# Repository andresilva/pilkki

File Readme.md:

# Pilkki
SWD flashing tool for EFM32 microcontrollers.

## Project structure

Utility to interact with flasher could be found in [software](software) folder.

Schematics and PCB (KiCAD) are in [electronics](electronics) folder.

Firmware sources are [here](firmware)

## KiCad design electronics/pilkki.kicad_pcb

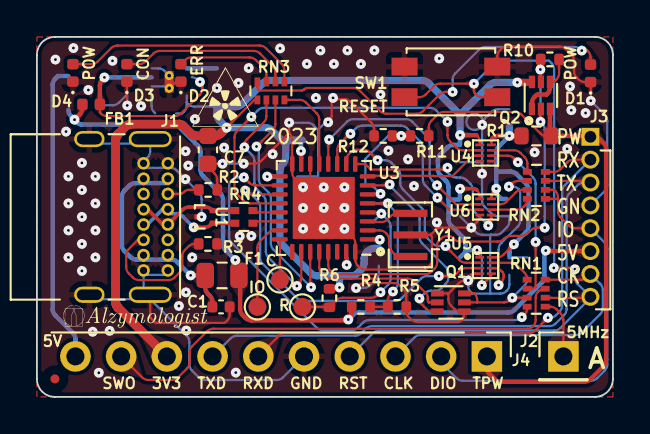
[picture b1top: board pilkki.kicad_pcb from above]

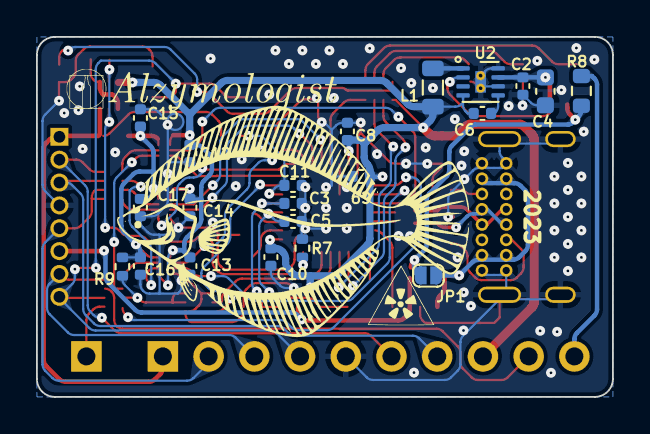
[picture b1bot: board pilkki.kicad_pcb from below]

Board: 2 copper layers, 32.0 x 20.0 mm, 58 parts (21 on the bottom side), 57 nets.

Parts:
C1, C2, C3, C5, C8, C9, C10, C11, C12, C13, C14, C15, C16, C17: 0.1u; C_0402_1005Metric
C4, C7: 4.7uFx6.3; C_0603_1608Metric
C6: 560pF; C_0402_1005Metric
D1: GREEN; LED_0402_1005Metric
D2: RED; LED_0402_1005Metric
D3: ORANGE; LED_0402_1005Metric
D4: YELLOW; LED_0402_1005Metric
F1: 0ZCK0100FF2E; Fuse_0805_2012Metric
FB1: BLM15AG102SZ1D; L_0402_1005Metric
FID1: Fiducial; Fiducial_0.5mm_Mask1.5mm
J1: USB_C_Receptacle; USB_C_Receptacle_GCT_USB4085
J2: Conn_01x01_Pin; PinHeader_1x01_P2.54mm_Vertical
J3: Conn_01x08; PinHeader_1x08_P1.27mm_Vertical
J4: Conn_01x10; PinHeader_1x10_P2.54mm_Vertical
JP1: SolderJumper_2_Open; SolderJumper_0.8.x1mm
L1: LQM21PN1R0MC0D; L_0805_2012Metric
Q1: SSM6N35AFE; SOT-563
Q2: DMG1023UV; SOT-563
R1: 10R; R_0603_1608Metric
R2, R3: 5.1K; R_0402_1005Metric
R4, R11: 4.7K; R_0402_1005Metric
R5, R6, R7, R9, R10, R12: 10K; R_0402_1005Metric
R8: 4.7R; R_0603_1608Metric
RN1, RN2: 100; R_Array_Concave_4x0402
RN3: 330; R_Array_Concave_4x0402
RN4: 33; R_Array_Convex_2x0402
SW1: EVQ-P2202M
SWDCK1: TestPoint; TestPoint_Pad_D1.0mm
SWDIO1: TestPoint; TestPoint_Pad_D1.0mm
U1: TPD2EUSB30A; Texas_DRT-3
U2: MIC23050-SYML; Micrel_MLF-8-1EP_2x2mm_P0.5mm_EP0.6x1.2mm_ThermalVias
U3: STM32G431KBUx; QFN-32-1EP_5x5mm_P0.5mm_EP3.45x3.45mm
U4, U5, U6: 74LVC2T45RA3; DFN1210-8
Y1: ECS-CTP-8.00-30; Resonator_SMD_Murata_CSTxExxV-3Pin_3.0x1.1mm

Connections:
3V3: C6.1, C7.2, C8.1, C9.1, C10.1, C12.1, C13.1, C14.1, J4.8, L1.2, Q2.6 (D), R6.2, RN3.5 (R4.2), U2.4 (SNS), U3.1 (VDD), U3.15 (VDDA), U3.17 (VDD), U4.1 (VCCA), U5.1 (VCCA), U5.5 (DIR), U6.1 (VCCA)
/CC1: J1.A5 (CC1), R2.2
/CC2: J1.B5 (CC2), R3.2
/D_N: J1.A7 (D-), J1.B7 (D-), RN4.1 (R1.1), U1.2 (D-)
/D_P: J1.A6 (D+), J1.B6 (D+), RN4.2 (R2.1), U1.1 (D+)
/LED0: RN3.8 (R1.2), U3.13 (PB0)
/LED1: RN3.6 (R3.2), U3.26 (PB3)
/LED2: RN3.7 (R2.2), U3.27 (PB4)
/PWRBR: Q2.2 (G), Q2.5 (G), R10.1, U3.29 (PB6)
/RST: J3.8, J4.4, RN1.2 (R2.1), SW1.2
/RXD: J3.2, J4.6, RN2.4 (R4.1)
/SWCLK: J3.7, J4.3, RN1.4 (R4.1)
/SWDIO: J3.5, J4.2, RN2.1 (R1.1), RN2.2 (R2.1)
/SWDIR: U3.9 (PA4), U6.5 (DIR)
/SWO: J4.9, RN1.3 (R3.1)
/TPWR_C: C11.1, R11.2, R12.1, U3.6 (PA1)
/TXD: J3.3, J4.7, RN2.3 (R3.1)
/V_BUS: C3.1, R4.2, R5.1, U3.5 (PA0)
/iMCO: RN1.8 (R1.2), U3.18 (PA8)
/iRST: Q1.2 (G), U3.28 (PB5)
/iRST_S: Q1.3 (D), U3.7 (PA2)
/iRXD: U3.20 (PA10), U4.2 (1A)
/iSWCLK: U3.10 (PA5), U5.2 (1A)
/iSWDIN: U3.11 (PA6), U6.3 (2A)
/iSWDO: U3.12 (PA7), U6.2 (1A)
/iSWO: U3.8 (PA3), U4.3 (2A)
/iTXD: U3.19 (PA9), U5.3 (2A)
/xRST: Q1.5 (G), Q1.6 (D), R9.1, RN1.7 (R2.2)
/xRXD: RN2.5 (R4.2), U4.7 (1B)
/xSWCLK: RN1.5 (R4.2), U5.7 (1B)
/xSWDIN: RN2.8 (R1.2), U6.6 (2B)
/xSWDO: RN2.7 (R2.2), U6.7 (1B)
/xSWO: RN1.6 (R3.2), U4.6 (2B)
/xTXD: RN2.6 (R3.2), U5.6 (2B)
GND: C1.2, C2.2, C3.2, C4.1, C5.2, C7.1, C8.2, C9.2, C10.2, C11.2, C12.2, C13.2, C14.2, C15.2, C16.2, C17.2, D1.1 (K), D2.1 (K), D3.1 (K), D4.1 (K), J1.A1 (GND), J1.A12 (GND), J1.B1 (GND), J1.B12 (GND), J1.S1 (SHIELD), J3.4, J4.5, Q1.1 (S), Q1.4 (S), R2.1, R3.1, R5.2, R7.1, R12.2, SW1.1, U1.3 (GND), U2.6 (AGND), U2.8 (PGND), U2.9 (EP_GND), U3.14 (VSSA), U3.16 (VSS), U3.32 (VSS), U3.33 (VSS), U4.4 (GND), U4.5 (DIR), U5.4 (GND), U6.4 (GND), Y1.2
unnamed: D1.2 (A), RN3.4 (R4.1)
unnamed: D2.2 (A), RN3.3 (R3.1)
unnamed: D3.2 (A), RN3.2 (R2.1)
unnamed: D4.2 (A), RN3.1 (R1.1)
unnamed: J2.1, RN1.1 (R1.1)
unnamed: J4.10, R8.1
unnamed: C1.1, F1.1, J1.A4 (VBUS), J1.A9 (VBUS), J1.B4 (VBUS), J1.B9 (VBUS), JP1.2 (B)
unnamed: Q2.1 (S), Q2.4 (S), R10.2
unnamed: RN4.4 (R1.2), U3.21 (PA11)
unnamed: RN4.3 (R2.2), U3.22 (PA12)
unnamed: C6.2, U2.5 (CFF)
unnamed: C2.1, C4.2, FB1.2, U2.2 (EN), U2.7 (VIN)
unnamed: L1.1, U2.1 (SW)
unnamed: SWDIO1.1, U3.23 (PA13)
unnamed: SWDCK1.1, U3.24 (PA14)
unnamed: R7.2, U3.31 (PB8)
unnamed: U3.2 (PF0), Y1.1
unnamed: U3.3 (PF1), Y1.3
unnamed: C5.1, R6.1, U3.4 (PG10)
TPWR: J3.1, J4.1, Q2.3 (D), R1.1, R11.1
USB_P: F1.2, FB1.1, J3.6, JP1.1 (A), R4.1, R8.2
xTPWR: C15.1, C16.1, C17.1, R1.2, R9.2, U4.8 (VCCB), U5.8 (VCCB), U6.8 (VCCB)

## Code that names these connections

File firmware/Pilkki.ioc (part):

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Mcu.Name=STM32G431K(6-8-B)Ux
Mcu.Package=UFQFPN32
Mcu.UserName=STM32G431KBUx
PA0.Mode=IN1-Single-Ended
PA0.Signal=ADC1_IN1
PA1.Mode=IN2-Single-Ended
PA1.Signal=ADC1_IN2
PA10.Mode=Asynchronous
PA10.Signal=USART1_RX
PA11.Mode=Device
PA11.Signal=USB_DM
PA12.Mode=Device
PA12.Signal=USB_DP
PA13.Mode=Serial_Wire
PA13.Signal=SYS_JTMS-SWDIO
PA14.Mode=Serial_Wire
PA14.Signal=SYS_JTCK-SWCLK
PA2.Mode=Asynchronous
PA2.Signal=USART2_TX
PA3.Mode=Asynchronous
PA3.Signal=USART2_RX
PA4.GPIOParameters=GPIO_Speed,PinState,GPIO_PuPd,GPIO_Label,GPIO_ModeDefaultOutputPP
PA4.GPIO_Label=SWDIR
PA4.GPIO_ModeDefaultOutputPP=GPIO_MODE_OUTPUT_PP
PA4.GPIO_PuPd=GPIO_NOPULL
PA4.GPIO_Speed=GPIO_SPEED_FREQ_VERY_HIGH
PA4.PinState=GPIO_PIN_RESET
PA4.Signal=GPIO_Output
PA5.GPIOParameters=GPIO_Speed
PA5.GPIO_Speed=GPIO_SPEED_FREQ_VERY_HIGH
PA5.Mode=Full_Duplex_Master
PA5.Signal=SPI1_SCK
PA6.GPIOParameters=GPIO_Speed,GPIO_PuPd
PA6.GPIO_PuPd=GPIO_PULLUP
PA6.GPIO_Speed=GPIO_SPEED_FREQ_VERY_HIGH
PA6.Mode=Full_Duplex_Master
PA6.Signal=SPI1_MISO
PA7.GPIOParameters=GPIO_Speed
PA7.GPIO_Speed=GPIO_SPEED_FREQ_VERY_HIGH
PA7.Mode=Full_Duplex_Master
PA7.Signal=SPI1_MOSI
PA8.Mode=Clock-out
PA8.Signal=RCC_MCO
PA9.Mode=Asynchronous
PA9.Signal=USART1_TX
PB0.GPIOParameters=GPIO_Label
PB0.GPIO_Label=LED0
PB0.Signal=GPIO_Output
PB3.GPIOParameters=GPIO_Label
PB3.GPIO_Label=LED1
PB3.Signal=GPIO_Output
PB4.GPIOParameters=GPIO_Label
PB4.GPIO_Label=LED2
PB4.Signal=GPIO_Output
PB5.GPIOParameters=GPIO_Label
PB5.GPIO_Label=iRST
PB5.Signal=GPIO_Output
PB6.GPIOParameters=PinState,GPIO_Label
PB6.GPIO_Label=PWR_BRR
PB6.PinState=GPIO_PIN_SET
PB6.Signal=GPIO_Output
PF0-OSC_IN.Mode=HSE-External-Oscillator
PF0-OSC_IN.Signal=RCC_OSC_IN
PF1-OSC_OUT.Mode=HSE-External-Oscillator
PF1-OSC_OUT.Signal=RCC_OSC_OUT
RCC.HSE_VALUE=20000000
RCC.SYSCLKFreq_VALUE=170000000
RCC.SYSCLKSource=RCC_SYSCLKSOURCE_PLLCLK
board=custom

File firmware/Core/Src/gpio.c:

/* USER CODE BEGIN Header */
/**
  ******************************************************************************
  * @file    gpio.c
  * @brief   This file provides code for the configuration
  *          of all used GPIO pins.
  ******************************************************************************
  * @attention
  *
  * Copyright (c) 2023 STMicroelectronics.
  * All rights reserved.
  *
  * This software is licensed under terms that can be found in the LICENSE file
  * in the root directory of this software component.
  * If no LICENSE file comes with this software, it is provided AS-IS.
  *
  ******************************************************************************
  */
/* USER CODE END Header */

/* Includes ------------------------------------------------------------------*/
#include "gpio.h"

/* USER CODE BEGIN 0 */

/* USER CODE END 0 */

/*----------------------------------------------------------------------------*/
/* Configure GPIO                                                             */
/*----------------------------------------------------------------------------*/
/* USER CODE BEGIN 1 */

/* USER CODE END 1 */

/** Configure pins as
        * Analog
        * Input
        * Output
        * EVENT_OUT
        * EXTI
        * Free pins are configured automatically as Analog (this feature is enabled through
        * the Code Generation settings)
     PA8   ------> RCC_MCO
*/
void MX_GPIO_Init(void)
{

  GPIO_InitTypeDef GPIO_InitStruct = {0};

  /* GPIO Ports Clock Enable */
  __HAL_RCC_GPIOF_CLK_ENABLE();
  __HAL_RCC_GPIOG_CLK_ENABLE();
  __HAL_RCC_GPIOA_CLK_ENABLE();
  __HAL_RCC_GPIOB_CLK_ENABLE();

  /*Configure GPIO pin Output Level */
  HAL_GPIO_WritePin(SWDIR_GPIO_Port, SWDIR_Pin, GPIO_PIN_RESET);

  /*Configure GPIO pin Output Level */
  HAL_GPIO_WritePin(GPIOB, LED0_Pin|LED1_Pin|LED2_Pin|iRST_Pin, GPIO_PIN_RESET);

  /*Configure GPIO pin Output Level */
  HAL_GPIO_WritePin(PWR_BRR_GPIO_Port, PWR_BRR_Pin, GPIO_PIN_SET);

  /*Configure GPIO pin : PG10 */
  GPIO_InitStruct.Pin = GPIO_PIN_10;
  GPIO_InitStruct.Mode = GPIO_MODE_ANALOG;
  GPIO_InitStruct.Pull = GPIO_NOPULL;
  HAL_GPIO_Init(GPIOG, &GPIO_InitStruct);

  /*Configure GPIO pin : PtPin */
  GPIO_InitStruct.Pin = SWDIR_Pin;
  GPIO_InitStruct.Mode = GPIO_MODE_OUTPUT_PP;
  GPIO_InitStruct.Pull = GPIO_NOPULL;
  GPIO_InitStruct.Speed = GPIO_SPEED_FREQ_VERY_HIGH;
  HAL_GPIO_Init(SWDIR_GPIO_Port, &GPIO_InitStruct);

  /*Configure GPIO pins : PBPin PBPin PBPin PBPin
                           PBPin */
  GPIO_InitStruct.Pin = LED0_Pin|LED1_Pin|LED2_Pin|iRST_Pin
                          |PWR_BRR_Pin;
  GPIO_InitStruct.Mode = GPIO_MODE_OUTPUT_PP;
  GPIO_InitStruct.Pull = GPIO_NOPULL;
  GPIO_InitStruct.Speed = GPIO_SPEED_FREQ_LOW;
  HAL_GPIO_Init(GPIOB, &GPIO_InitStruct);

  /*Configure GPIO pin : PA8 */
  GPIO_InitStruct.Pin = GPIO_PIN_8;
  GPIO_InitStruct.Mode = GPIO_MODE_AF_PP;
  GPIO_InitStruct.Pull = GPIO_NOPULL;
  GPIO_InitStruct.Speed = GPIO_SPEED_FREQ_LOW;
  GPIO_InitStruct.Alternate = GPIO_AF0_MCO;
  HAL_GPIO_Init(GPIOA, &GPIO_InitStruct);

  /*Configure GPIO pin : PA15 */
  GPIO_InitStruct.Pin = GPIO_PIN_15;
  GPIO_InitStruct.Mode = GPIO_MODE_ANALOG;
  GPIO_InitStruct.Pull = GPIO_NOPULL;
  HAL_GPIO_Init(GPIOA, &GPIO_InitStruct);

  /*Configure GPIO pins : PB7 PB8 */
  GPIO_InitStruct.Pin = GPIO_PIN_7|GPIO_PIN_8;
  GPIO_InitStruct.Mode = GPIO_MODE_ANALOG;
  GPIO_InitStruct.Pull = GPIO_NOPULL;
  HAL_GPIO_Init(GPIOB, &GPIO_InitStruct);

}

/* USER CODE BEGIN 2 */

/* USER CODE END 2 */

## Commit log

2023-08-12 Basic implementation & linux support
2023-08-12 Add readme
2023-08-16 Give a name to the project, reorganize to store hardware and firmware files
2023-08-21 Add schematics and firmware sources (code only, not buildable yet)
2023-09-14 Added a GPLv3 license, to match the rest of our projects
2023-09-18 Add automatic reset after flashing
2023-10-26 Build firmware with cmake
2023-10-27 Finalize firmware build
2023-11-05 Pilkki utility cicd, win&macos implementations, code cleanup, deps via FetchContent (#1)
    * Create pilkki-software-multiplatform.yml
    * Windows and MacOS implementations
    * Code cleanup
    * Use FetchContent instead of submodules
2023-11-07 Unified serial impl for unix family, fixed termios flags (#2)
2023-11-29 Update Readme.md
    How to install in Ubuntu w/o SMS & registration
2023-12-09 rewritten flasher utility readme, added macos steps
2023-12-10 added autodetect macos port implementation (#5)
2024-01-30 nixify
